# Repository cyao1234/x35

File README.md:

# x35 devboard

Why? IDFK blame max. I am in their basement help. ch32x350 devboard w/ usb pd and 24v tolerance u can use this to negotate pd or whatever it uses a mcu just do mcu things brrrrrrr

Features:
- Tiny footprint
- Tiny footprint *2
- usb pd
- usb bootloader so no max in a basement :c 
- i'm going crazy 

3d pic too

heres a virtual bom that's useless

| item | price|
| --|--|
|pcb pcba | $70|

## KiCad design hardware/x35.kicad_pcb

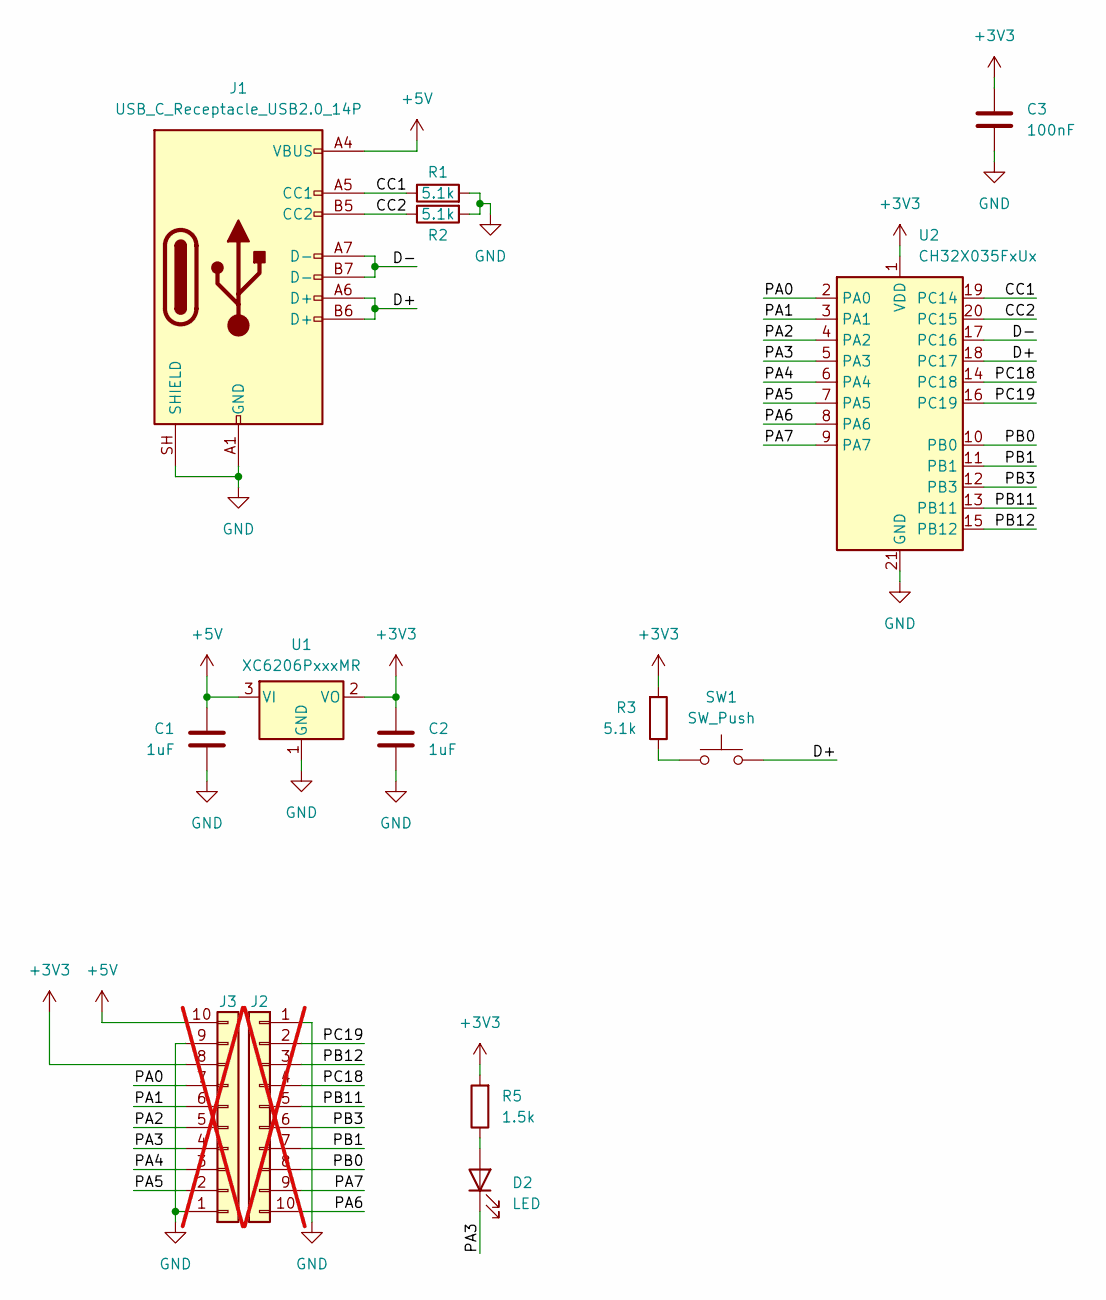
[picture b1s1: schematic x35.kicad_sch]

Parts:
C1, C2: 1uF; C_0402_1005Metric; LCSC Part # C52923
C3: 100nF; C_0402_1005Metric; LCSC Part # C100072
D2: LED; LED_0402_1005Metric; LCSC Part # C965793
J1: USB_C_Receptacle_USB2.0_14P; USB_C_Receptacle_HRO_TYPE-C-31-M-12; LCSC Part # C393939
J2, J3: Conn_01x10; Castellated_1x10_P2.54mm_Vertical; not fitted
R1, R2, R3: 5.1k; R_0402_1005Metric; LCSC Part # C25905
R5: 1.5k; R_0402_1005Metric; LCSC Part # C25867
SW1: SW_Push; SW_Push_SPST_TSA016; LCSC Part # C2888427
U1: XC6206PxxxMR; SOT-23-3; LCSC Part # C54279900
U2: CH32X035FxUx; QFN-20-1EP_3x3mm_P0.4mm_EP1.65x1.65mm; LCSC Part # C42442062

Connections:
+3V3: C2.1, C3.1, J3.8, R3.2, R5.2, U1.2 (VO), U2.1 (VDD)
+5V: C1.1, J1.A4 (VBUS), J1.A9 (VBUS), J1.B4 (VBUS), J1.B9 (VBUS), J3.10, U1.3 (VI)
/CC1: J1.A5 (CC1), R1.1, U2.19 (CC1)
/CC2: J1.B5 (CC2), R2.1, U2.20 (CC2)
/D+: J1.A6 (D+), J1.B6 (D+), SW1.2, U2.18 (D+)
/D-: J1.A7 (D-), J1.B7 (D-), U2.17 (D-)
/PA0: J3.7, U2.2 (PA0)
/PA1: J3.6, U2.3 (PA1)
/PA2: J3.5, U2.4 (PA2)
/PA3: D2.1 (K), J3.4, U2.5 (PA3)
/PA4: J3.3, U2.6 (PA4)
/PA5: J3.2, U2.7 (PA5)
/PA6: J2.10, U2.8 (PA6)
/PA7: J2.9, U2.9 (PA7)
/PB0: J2.8, U2.10 (PB0)
/PB1: J2.7, U2.11 (PB1)
/PB3: J2.6, U2.12 (PB3)
/PB11: J2.5, U2.13 (PB11)
/PB12: J2.3, U2.15 (PB12)
/PC18: J2.4, U2.14 (PC18)
/PC19: J2.2, U2.16 (PC19)
GND: C1.2, C2.2, C3.2, J1.A1 (GND), J1.A12 (GND), J1.B1 (GND), J1.B12 (GND), J1.SH (SHIELD), J2.1, J3.1, J3.9, R1.2, R2.2, U1.1 (GND), U2.21 (GND)
unnamed: D2.2 (A), R5.1
unnamed: R3.1, SW1.1

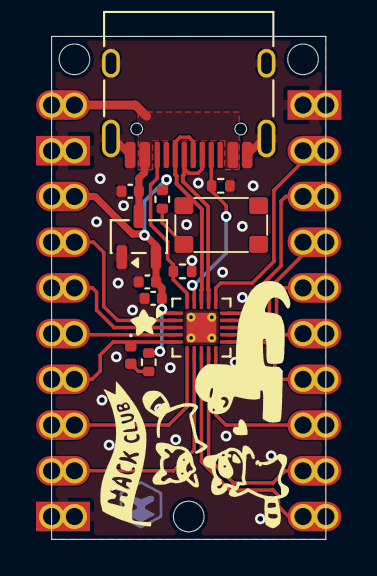
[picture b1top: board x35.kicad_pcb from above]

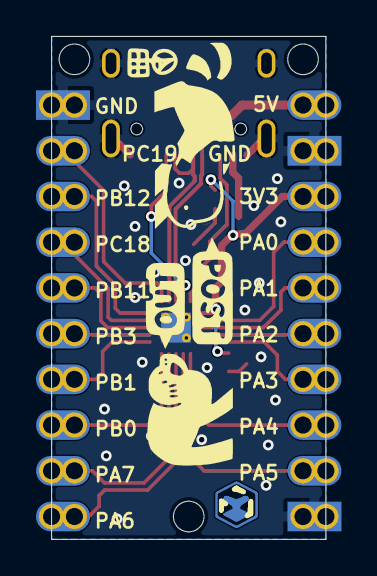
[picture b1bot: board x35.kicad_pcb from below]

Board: 2 copper layers, 15.2 x 27.9 mm, 14 parts (2 on the bottom side), 24 nets.

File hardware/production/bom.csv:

Designator,Footprint,Quantity,Value,LCSC Part #
"C1, C2",0402,2,1uF,C52923 
C3,0402,1,100nF,C100072
D2,0402,1,LED,C965793
J1,USB_C_Receptacle_HRO_TYPE-C-31-M-12,1,USB_C_Receptacle_USB2.0_14P,C393939
"R1, R2, R3",0402,3,5.1k,C25905
R5,0402,1,1.5k,C25867
SW1,SW_Push_SPST_TSA016,1,SW_Push,C2888427
U1,SOT-23-3,1,XC6206PxxxMR,C54279900
U2,QFN-20-1EP_3x3mm_P0.4mm_EP1.65x1.65mm_ThermalVias,1,CH32X035x8x6,C42442062
